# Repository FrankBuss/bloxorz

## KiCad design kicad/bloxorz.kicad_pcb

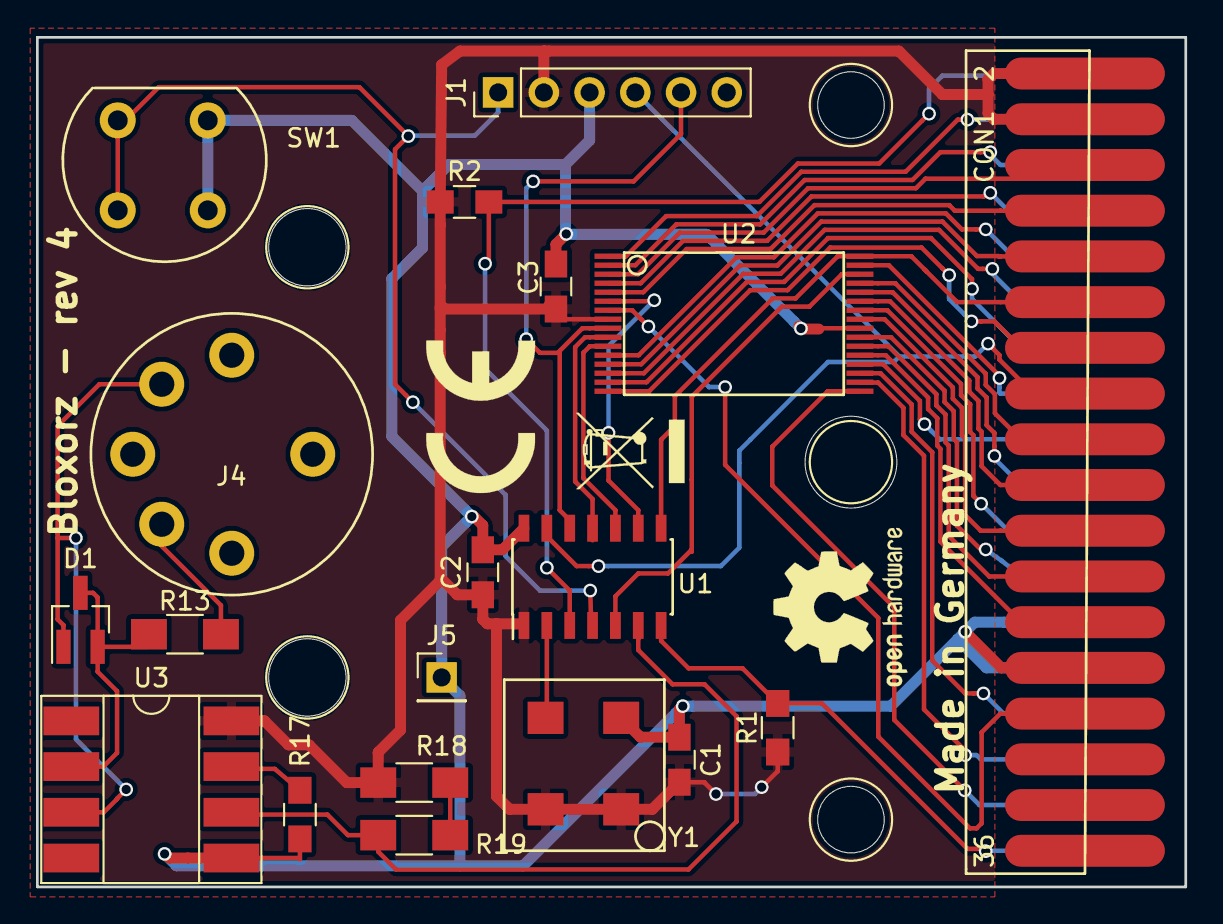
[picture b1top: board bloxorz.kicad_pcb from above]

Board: 2 copper layers, 63.8 x 47.2 mm, 24 parts (0 on the bottom side), 43 nets.

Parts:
C1, C2, C3: 100n; C_0805_HandSoldering
CON1: vectrex-edge-connector; vectrex
D1: BAV99; SOT-23_Handsoldering
J1: PICKIT; Pin_Header_Straight_1x06_Pitch2.54mm
J4: DIN_5; din5
J5: GND; Pin_Header_Straight_1x01_Pitch2.54mm
R1, R2, R17: 10k; R_0805_HandSoldering
R13, R18, R19: 220; R_1206_HandSoldering
SW1: SW_DPST; button
U1: PIC16F18323; SOIC-14_3.9x8.7mm_Pitch1.27mm
U2: SST39SF040-TSOP; TSOP32WH
U3: 6N135; DIP-8_W8.89mm_SMDSocket_LongPads
Y1: 8 MHz oscillator; oscillator
hole1, hole2, hole3, hole4, hole5: 1pin

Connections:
+5V: C1.2, C2.1, C3.2, CON1.2, CON1.4, J1.2, R1.1, R2.1, R18.1, U1.1, U2.8, U3.8, Y1.1, Y1.4
A0: CON1.17, U2.20
A1: CON1.15, U2.31
A2: CON1.13, U2.15
A3: CON1.11, U2.14
A4: CON1.9, U2.12
A5: CON1.7, U2.4
A6: CON1.5, U2.2
A7: CON1.3, U2.1
A8: CON1.6, U2.3
A9: CON1.8, U2.5
A10: CON1.14, U2.16
A11: CON1.10, U2.13
A12: CON1.29, U2.19
A13: CON1.31, U2.18
A14: CON1.33, U2.17
A15: U1.10, U2.11
A16: U1.11, U2.10
A17: U1.9, U2.6
A18: J1.5, U1.12, U2.9
D0: CON1.19, U2.28
D1: CON1.21, U2.26
D2: CON1.23, U2.23
D3: CON1.26, U2.21
D4: CON1.24, U2.22
D5: CON1.22, U2.25
D6: CON1.20, U2.27
D7: CON1.18, U2.29
GND: C1.1, C2.2, C3.1, CON1.25, CON1.27, CON1.28, J1.3, J5.1, R17.2, SW1.2, SW1.4, U1.14, U2.24, U3.5, Y1.2
unnamed: D1.1, J4.5, U3.3
unnamed: D1.2, D1.3, R13.1, U3.2
unnamed: J1.1, SW1.1, SW1.3, U1.4
unnamed: J4.4, R13.2
unnamed: R17.1, U3.7
unnamed: R18.2, R19.1
unnamed: R19.2, U1.6, U3.6
unnamed: U1.2, Y1.3
unnamed: U1.5, U2.30
V-CE: CON1.16, J1.4, U1.13
V-HALT: CON1.1, R2.2, U1.3
V-OE: CON1.12, U1.8, U2.32
V-PB6: CON1.35, R1.2, U1.7
V-RW: CON1.30, U2.7

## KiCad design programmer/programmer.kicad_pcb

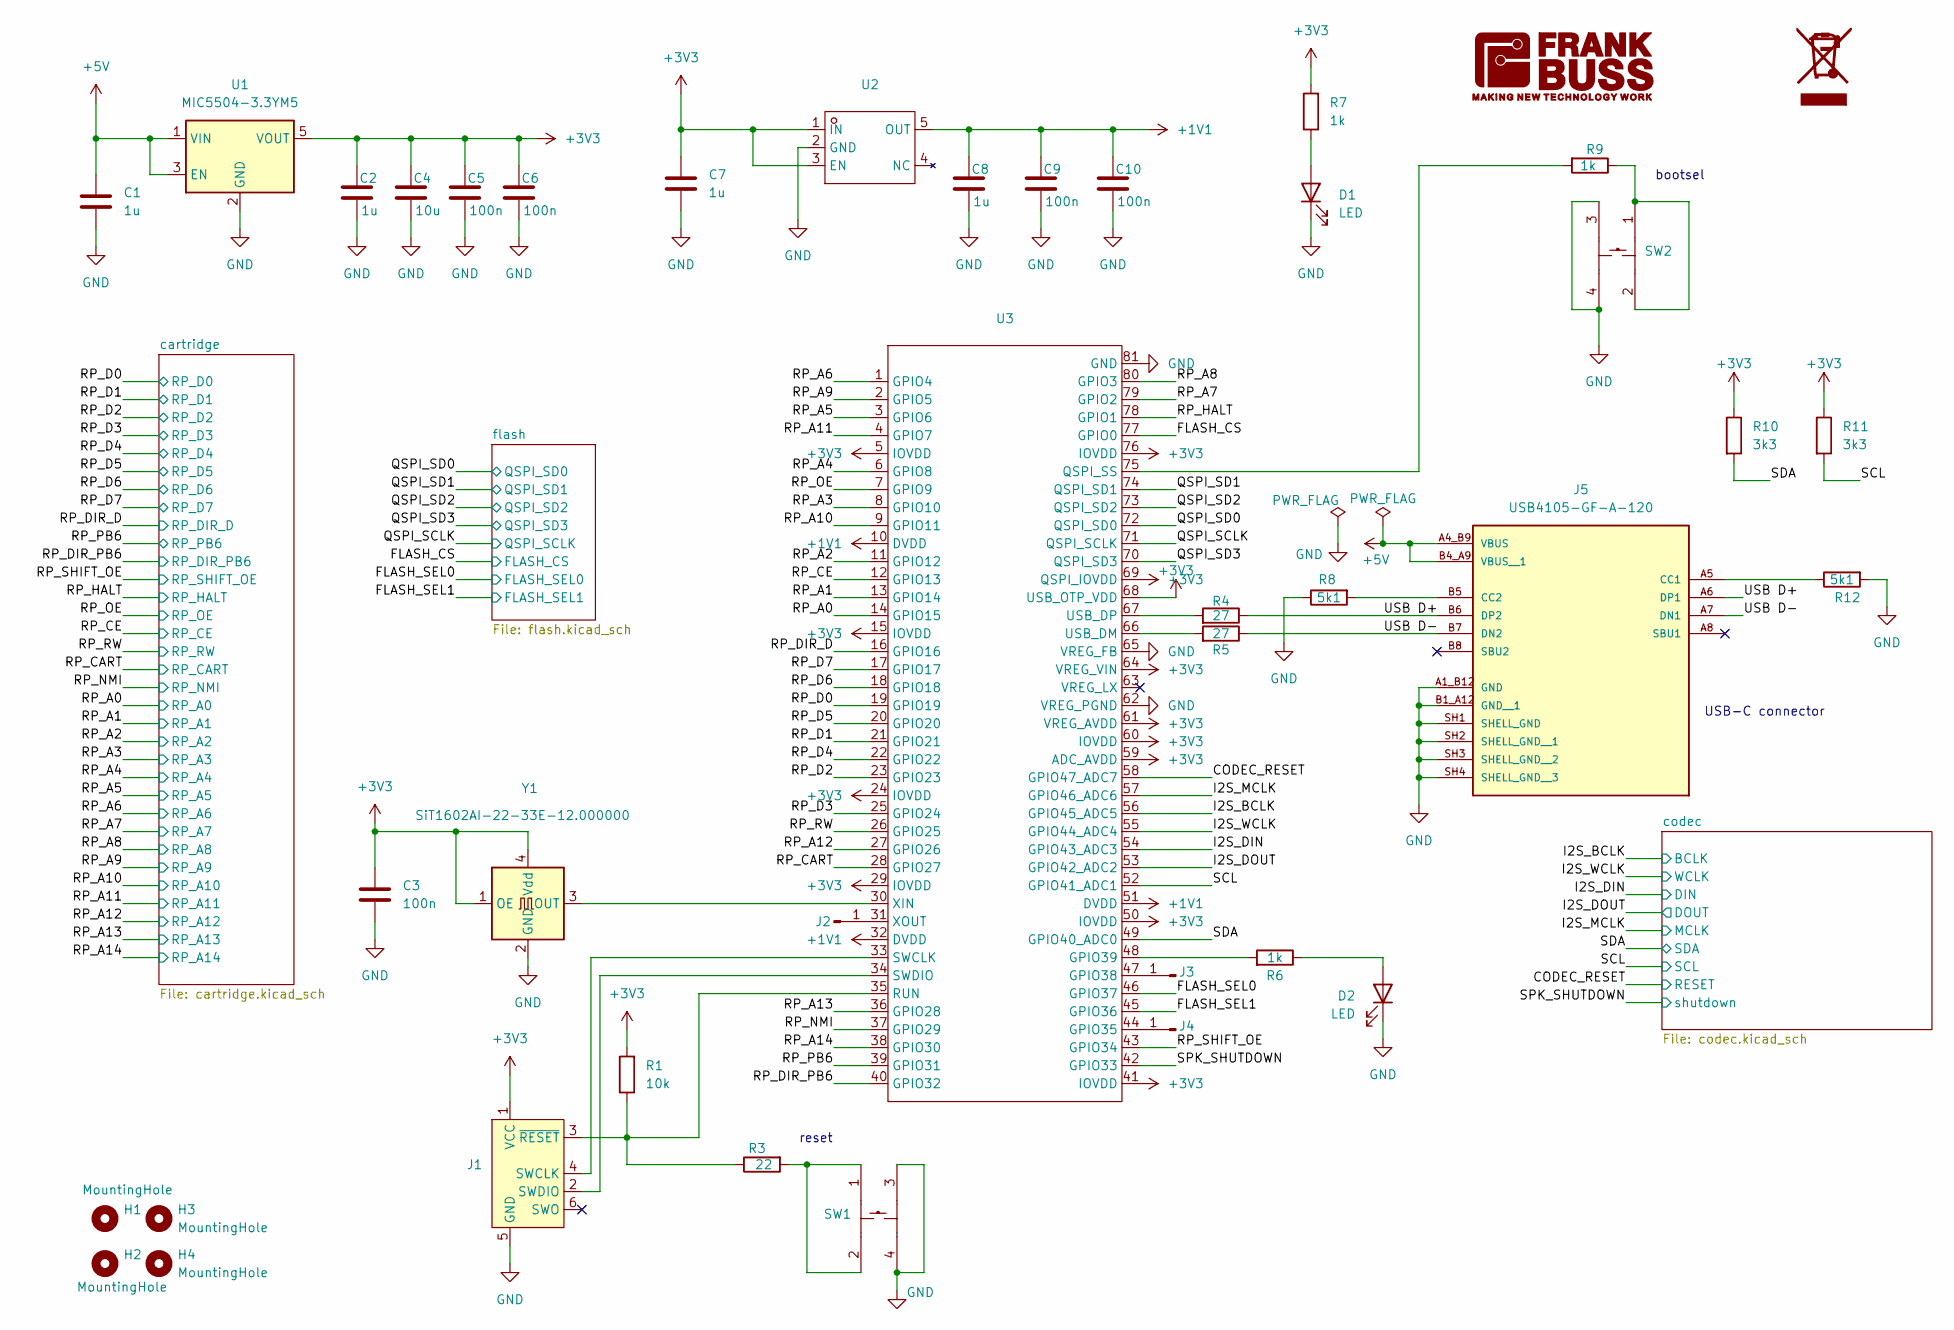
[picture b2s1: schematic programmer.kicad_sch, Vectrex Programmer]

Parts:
C1, C2, C8: 1u; C_0805_2012Metric
C3: 100n; C_0603_1608Metric
C4: 10u; C_0805_2012Metric
C5, C6, C9, C10: 100n; C_0805_2012Metric
C7: 1u; C_0603_1608Metric
D1, D2: LED; LED_0805_2012Metric
G1: Logo_WEEE; WEEE-Logo_8.4x12mm_SilkScreen
G2: Logo_FrankBuss; frank-buss-logo
H1, H2, H3, H4: MountingHole; MountingHole_3.2mm_M3
J1: Conn_ARM_SWD_TagConnect_TC2030-NL; Tag-Connect_TC2030-IDC-NL_2x03_P1.27mm_Vertical
J2, J3, J4: Conn_01x01_Pin; PinHeader_1x01_P2.54mm_Vertical
J5: USB4105-GF-A-120; GCT_USB4105-GF-A-120; PARTREV B3
R1: 10k; R_0603_1608Metric
R3: 22; R_0603_1608Metric
R4, R5: 27; R_0603_1608Metric
R6, R7, R9: 1k; R_0603_1608Metric
R8, R12: 5k1; R_0603_1608Metric
R10, R11: 3k3; R_0603_1608Metric
SW1, SW2: KEY-SMD_4P-L6.0-W6.0-P4.50-LS9.0; Manufacturer Part TS-1002S-07026C; LCSC Part Name 6*6*7mm 立贴 轻触开关
U1: MIC5504-3.3YM5; SOT-23-5
U2: SOT-23-5_L3.0-W1.7-P0.95-LS2.8-BL; Manufacturer Part TLV74311PDBVR; LCSC Part Name 具有使能功能的 300mA、低 IQ、低压降稳压器
U3: QFN-80_L10.0-W10.0-P0.40-TL-EP3.4; Manufacturer Part RP2354B; LCSC Part Name RP2354B
Y1: SiT1602AI-22-33E-12.000000; Oscillator_SMD_SiTime_SiT1602-4Pin_3.2x2.5mm; MPN SiT1602AI-22-33E-12.000000; LCSC C830041

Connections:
+1V1: C8.1, C9.1, C10.1, U2.5 (OUT), U3.10 (DVDD), U3.32 (DVDD), U3.51 (DVDD)
+3V3: C2.1, C3.1, C4.1, C5.1, C6.1, C7.1, J1.1 (VCC), R1.2, R7.2, R10.1, R11.1, U1.5 (VOUT), U2.1 (IN), U2.3 (EN), U3.5 (IOVDD), U3.15 (IOVDD), U3.24 (IOVDD), U3.29 (IOVDD), U3.41 (IOVDD), U3.50 (IOVDD), U3.59 (ADC_AVDD), U3.60 (IOVDD), U3.61 (VREG_AVDD), U3.64 (VREG_VIN), U3.68 (USB_OTP_VDD), U3.69 (QSPI_IOVDD), U3.76 (IOVDD), Y1.1 (OE), Y1.4 (Vdd); also elsewhere on the board
+5V: C1.1, J5.A4_B9 (VBUS), J5.B4_A9 (VBUS__1), U1.1 (VIN), U1.3 (EN); also elsewhere on the board
/CODEC_RESET: U3.58 (GPIO47_ADC7); also elsewhere on the board
/FLASH_CS: U3.77 (GPIO0); also elsewhere on the board
/FLASH_SEL0: U3.46 (GPIO37); also elsewhere on the board
/FLASH_SEL1: U3.45 (GPIO36); also elsewhere on the board
/I2S_BCLK: U3.56 (GPIO45_ADC5); also elsewhere on the board
/I2S_DIN: U3.54 (GPIO43_ADC3); also elsewhere on the board
/I2S_DOUT: U3.53 (GPIO42_ADC2); also elsewhere on the board
/I2S_MCLK: U3.57 (GPIO46_ADC6); also elsewhere on the board
/I2S_WCLK: U3.55 (GPIO44_ADC4); also elsewhere on the board
/QSPI_SCLK: U3.71 (QSPI_SCLK); also elsewhere on the board
/QSPI_SD0: U3.72 (QSPI_SD0); also elsewhere on the board
/QSPI_SD1: U3.74 (QSPI_SD1); also elsewhere on the board
/QSPI_SD2: U3.73 (QSPI_SD2); also elsewhere on the board
/QSPI_SD3: U3.70 (QSPI_SD3); also elsewhere on the board
/RP_A0: U3.14 (GPIO15); also elsewhere on the board
/RP_A1: U3.13 (GPIO14); also elsewhere on the board
/RP_A2: U3.11 (GPIO12); also elsewhere on the board
/RP_A3: U3.8 (GPIO10); also elsewhere on the board
/RP_A4: U3.6 (GPIO8); also elsewhere on the board
/RP_A5: U3.3 (GPIO6); also elsewhere on the board
/RP_A6: U3.1 (GPIO4); also elsewhere on the board
/RP_A7: U3.79 (GPIO2); also elsewhere on the board
/RP_A8: U3.80 (GPIO3); also elsewhere on the board
/RP_A9: U3.2 (GPIO5); also elsewhere on the board
/RP_A10: U3.9 (GPIO11); also elsewhere on the board
/RP_A11: U3.4 (GPIO7); also elsewhere on the board
/RP_A12: U3.27 (GPIO26); also elsewhere on the board
/RP_A13: U3.36 (GPIO28); also elsewhere on the board
/RP_A14: U3.38 (GPIO30); also elsewhere on the board
/RP_CART: U3.28 (GPIO27); also elsewhere on the board
/RP_CE: U3.12 (GPIO13); also elsewhere on the board
/RP_D0: U3.19 (GPIO19); also elsewhere on the board
/RP_D1: U3.21 (GPIO21); also elsewhere on the board
/RP_D2: U3.23 (GPIO23); also elsewhere on the board
/RP_D3: U3.25 (GPIO24); also elsewhere on the board
/RP_D4: U3.22 (GPIO22); also elsewhere on the board
/RP_D5: U3.20 (GPIO20); also elsewhere on the board
/RP_D6: U3.18 (GPIO18); also elsewhere on the board
/RP_D7: U3.17 (GPIO17); also elsewhere on the board
/RP_DIR_D: U3.16 (GPIO16); also elsewhere on the board
/RP_DIR_PB6: U3.40 (GPIO32); also elsewhere on the board
/RP_HALT: U3.78 (GPIO1); also elsewhere on the board
/RP_NMI: U3.37 (GPIO29); also elsewhere on the board
/RP_OE: U3.7 (GPIO9); also elsewhere on the board
/RP_PB6: U3.39 (GPIO31); also elsewhere on the board
/RP_RW: U3.26 (GPIO25); also elsewhere on the board
/RP_SHIFT_OE: U3.43 (GPIO34); also elsewhere on the board
/SCL: R11.2, U3.52 (GPIO41_ADC1); also elsewhere on the board
/SDA: R10.2, U3.49 (GPIO40_ADC0); also elsewhere on the board
/SPK_SHUTDOWN: U3.42 (GPIO33); also elsewhere on the board
/USB D+: J5.A6 (DP1), J5.B6 (DP2), R4.1
/USB D-: J5.A7 (DN1), J5.B7 (DN2), R5.1
GND: C1.2, C2.2, C3.2, C4.2, C5.2, C6.2, C7.2, C8.2, C9.2, C10.2, D1.1 (K), D2.1 (K), J1.5 (GND), J5.A1_B12 (GND), J5.B1_A12 (GND__1), J5.SH1 (SHELL_GND), J5.SH2 (SHELL_GND__1), J5.SH3 (SHELL_GND__2), J5.SH4 (SHELL_GND__3), R8.1, R12.2, SW1.3, SW1.4, SW2.3, SW2.4, U1.2 (GND), U2.2 (GND), U3.62 (VREG_PGND), U3.65 (VREG_FB), U3.81 (GND), Y1.2 (GND); also elsewhere on the board
unnamed: D1.2 (A), R7.1
unnamed: D2.2 (A), R6.1
unnamed: J1.4 (SWCLK), U3.33 (SWCLK)
unnamed: J1.2 (SWDIO), U3.34 (SWDIO)
unnamed: J1.3 (~RESET), R1.1, R3.1, U3.35 (RUN)
unnamed: J2.1, U3.31 (XOUT)
unnamed: J3.1, U3.47 (GPIO38)
unnamed: J4.1, U3.44 (GPIO35)
unnamed: J5.A5 (CC1), R12.1
unnamed: J5.B5 (CC2), R8.2
unnamed: R3.2, SW1.1, SW1.2
unnamed: R9.1, SW2.1, SW2.2
unnamed: R6.2, U3.48 (GPIO39)
unnamed: R9.2, U3.75 (QSPI_SS)
unnamed: R5.2, U3.66 (USB_DM)
unnamed: R4.2, U3.67 (USB_DP)
unnamed: U3.30 (XIN), Y1.3 (OUT)

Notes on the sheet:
bootsel
reset
USB-C connector

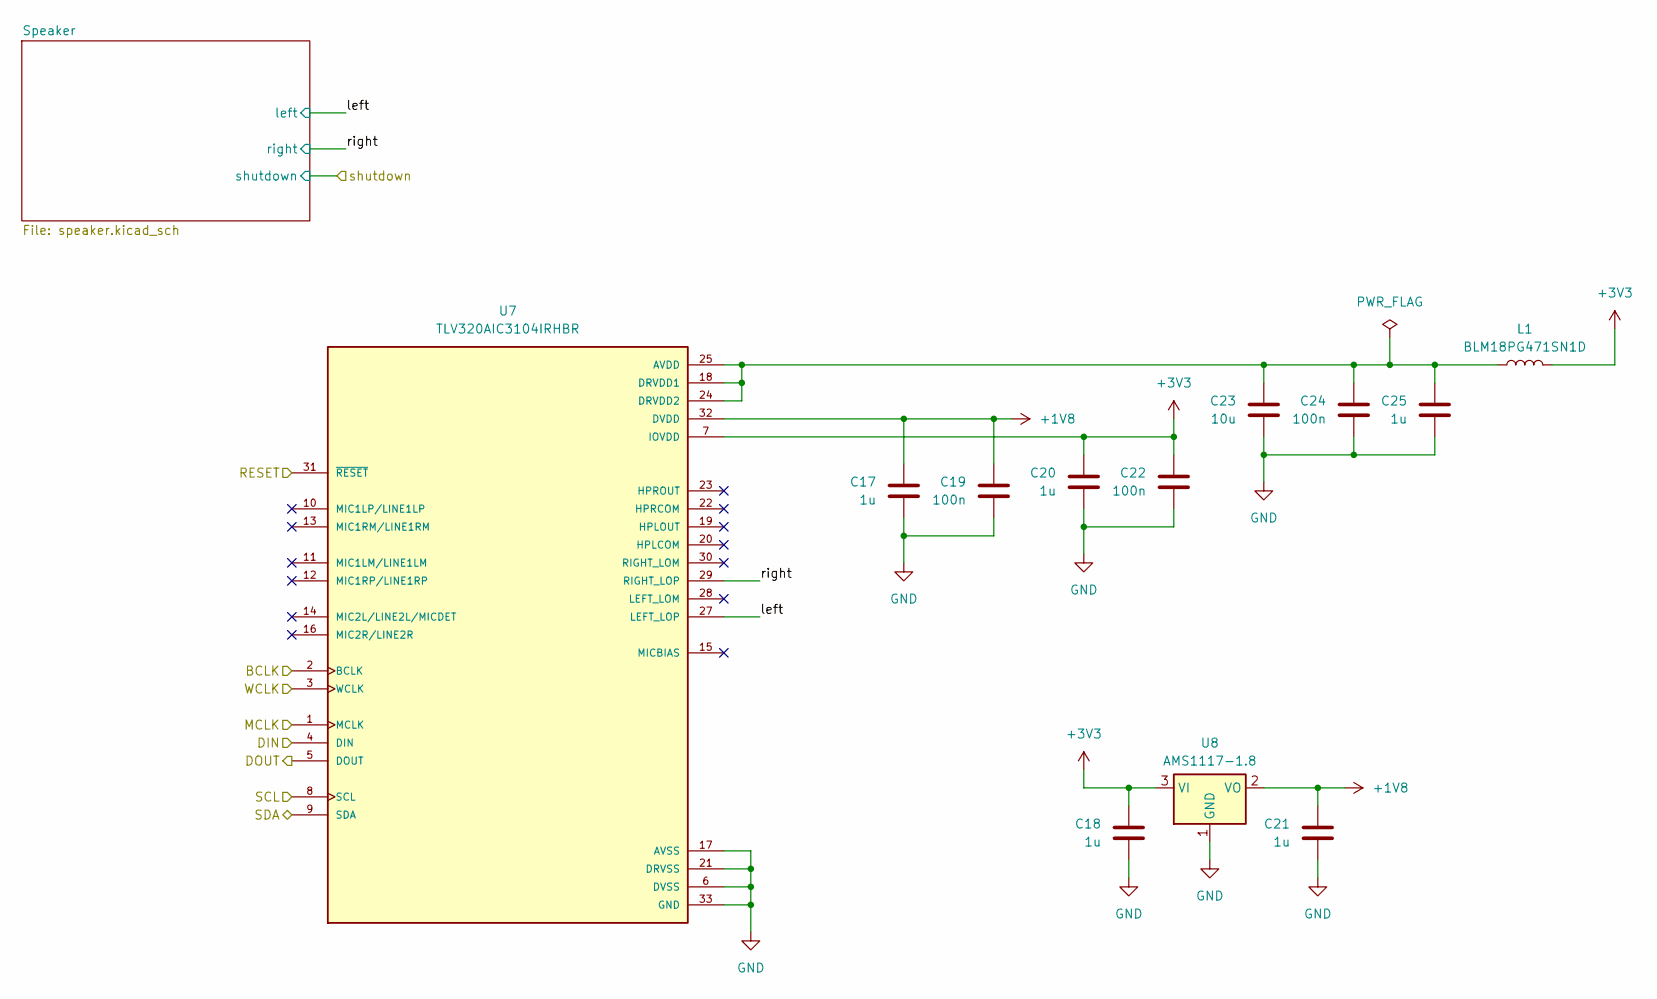
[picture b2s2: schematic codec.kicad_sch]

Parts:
C17, C18, C20, C21, C25: 1u; C_0603_1608Metric
C19, C22, C24: 100n; C_0603_1608Metric
C23: 10u; C_0603_1608Metric
L1: BLM18PG471SN1D; L_0603_1608Metric
U7: TLV320AIC3104IRHBR; QFN50P500X500X100-33N; DigiKey_Part_Number 296-26818-1-ND
U8: AMS1117-1.8; SOT-223-3_TabPin2

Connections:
+1V8: C17.1, C19.1, C21.1, U7.32 (DVDD), U8.2 (VO)
+3V3: C18.1, C20.1, C22.1, L1.1, U7.7 (IOVDD), U8.3 (VI); also elsewhere on the board
/CODEC_RESET: U7.31 (~RESET); also elsewhere on the board
/I2S_BCLK: U7.2 (BCLK); also elsewhere on the board
/I2S_DIN: U7.4 (DIN); also elsewhere on the board
/I2S_DOUT: U7.5 (DOUT); also elsewhere on the board
/I2S_MCLK: U7.1 (MCLK); also elsewhere on the board
/I2S_WCLK: U7.3 (WCLK); also elsewhere on the board
/SCL: U7.8 (SCL); also elsewhere on the board
/SDA: U7.9 (SDA); also elsewhere on the board
/codec/left: U7.27 (LEFT_LOP); also elsewhere on the board
/codec/right: U7.29 (RIGHT_LOP); also elsewhere on the board
GND: C17.2, C18.2, C19.2, C20.2, C21.2, C22.2, C23.2, C24.2, C25.2, U7.6 (DVSS), U7.17 (AVSS), U7.21 (DRVSS), U7.26 (GND), U7.33 (GND), U7.33_1 (GND), U7.33_2 (GND), U7.33_3 (GND), U7.33_4 (GND), U7.33_5 (GND), U7.33_6 (GND), U7.33_7 (GND), U7.33_8 (GND), U7.33_9 (GND), U8.1 (GND); also elsewhere on the board
unnamed: C23.1, C24.1, C25.1, L1.2, U7.18 (DRVDD1), U7.24 (DRVDD2), U7.25 (AVDD)

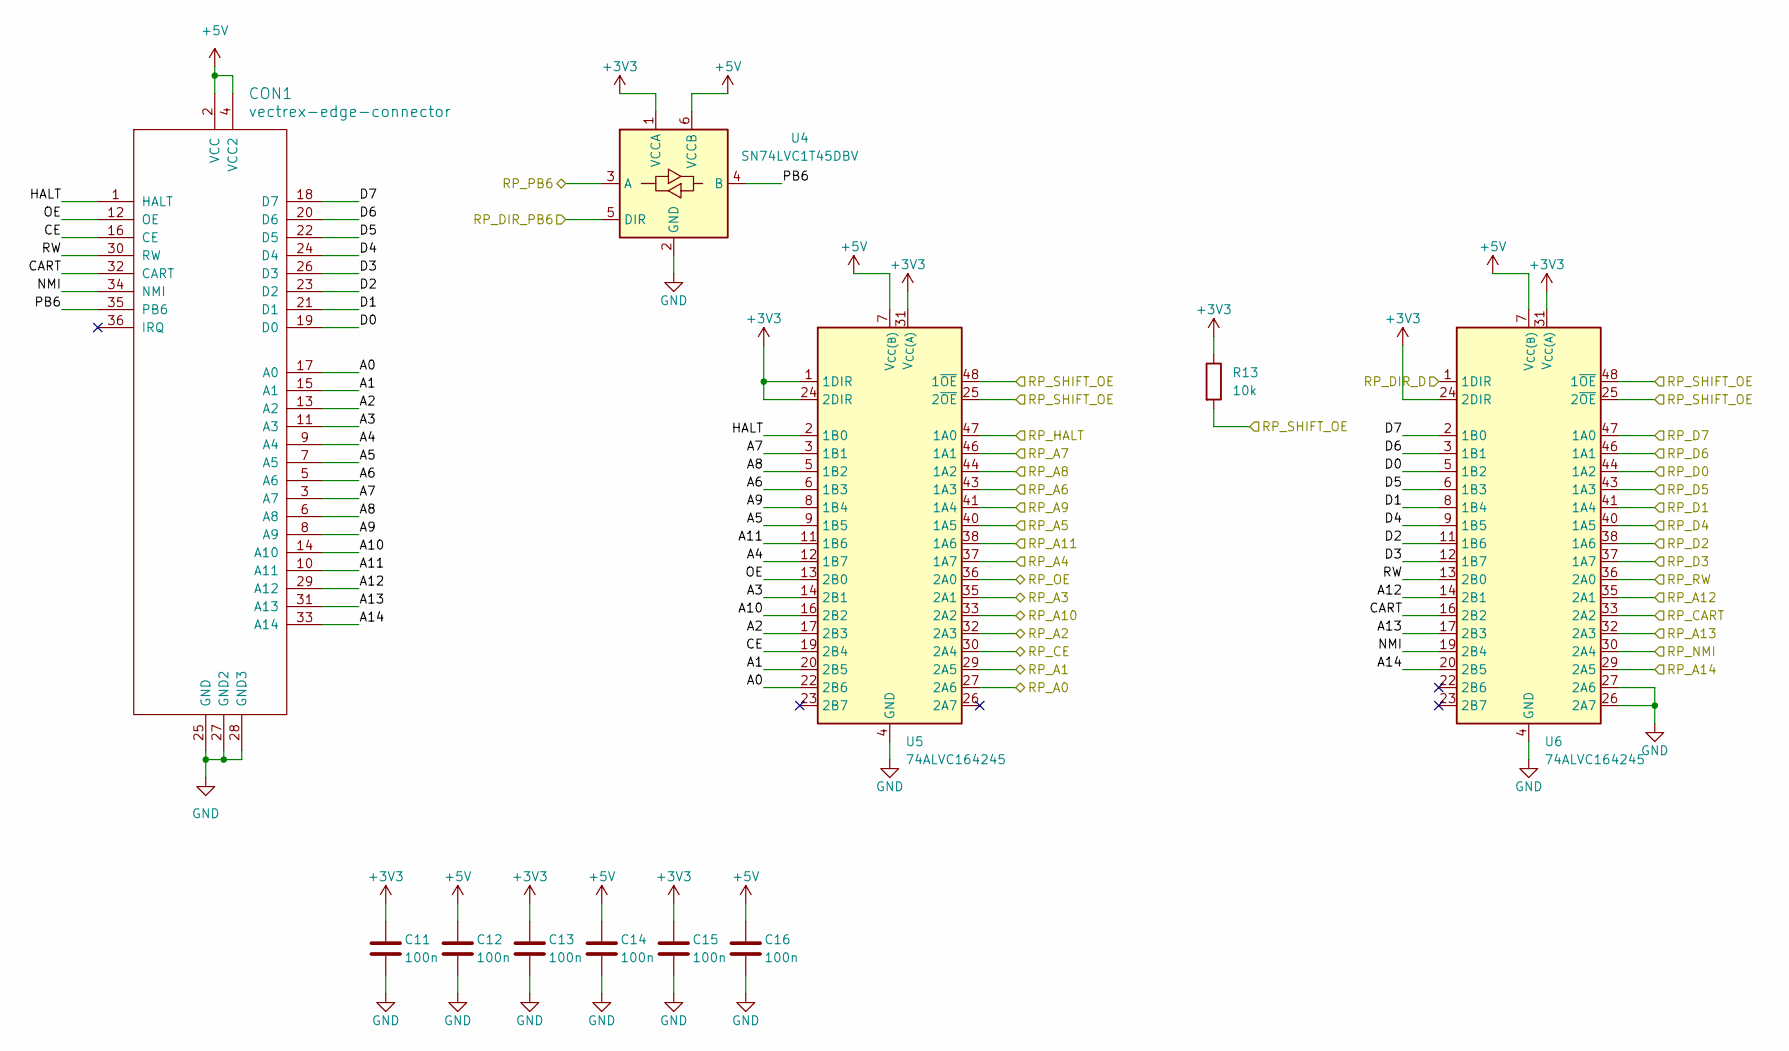
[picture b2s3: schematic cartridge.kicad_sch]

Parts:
C11, C12, C13, C14, C15, C16: 100n; C_0603_1608Metric
CON1: vectrex-edge-connector; vectrex; MPN WingTAT ED36BGFBK; LCSC C5173302
R13: 10k; R_0603_1608Metric
U4: SN74LVC1T45DBV; SOT-23-6
U5, U6: 74ALVC164245; TSSOP-48_6.1x12.5mm_P0.5mm

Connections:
+3V3: C11.1, C13.1, C15.1, R13.1, U4.1 (VCCA), U5.1 (1DIR), U5.24 (2DIR), U5.31 (V_{CC(A)}), U5.42 (V_{CC(A)}), U6.24 (2DIR), U6.31 (V_{CC(A)}), U6.42 (V_{CC(A)}); also elsewhere on the board
+5V: C12.1, C14.1, C16.1, CON1.2 (VCC), CON1.4 (VCC2), U4.6 (VCCB), U5.7 (V_{CC(B)}), U5.18 (V_{CC(B)}), U6.7 (V_{CC(B)}), U6.18 (V_{CC(B)}); also elsewhere on the board
/RP_A0: U5.27 (2A6); also elsewhere on the board
/RP_A1: U5.29 (2A5); also elsewhere on the board
/RP_A2: U5.32 (2A3); also elsewhere on the board
/RP_A3: U5.35 (2A1); also elsewhere on the board
/RP_A4: U5.37 (1A7); also elsewhere on the board
/RP_A5: U5.40 (1A5); also elsewhere on the board
/RP_A6: U5.43 (1A3); also elsewhere on the board
/RP_A7: U5.46 (1A1); also elsewhere on the board
/RP_A8: U5.44 (1A2); also elsewhere on the board
/RP_A9: U5.41 (1A4); also elsewhere on the board
/RP_A10: U5.33 (2A2); also elsewhere on the board
/RP_A11: U5.38 (1A6); also elsewhere on the board
/RP_A12: U6.35 (2A1); also elsewhere on the board
/RP_A13: U6.32 (2A3); also elsewhere on the board
/RP_A14: U6.29 (2A5); also elsewhere on the board
/RP_CART: U6.33 (2A2); also elsewhere on the board
/RP_CE: U5.30 (2A4); also elsewhere on the board
/RP_D0: U6.44 (1A2); also elsewhere on the board
/RP_D1: U6.41 (1A4); also elsewhere on the board
/RP_D2: U6.38 (1A6); also elsewhere on the board
/RP_D3: U6.37 (1A7); also elsewhere on the board
/RP_D4: U6.40 (1A5); also elsewhere on the board
/RP_D5: U6.43 (1A3); also elsewhere on the board
/RP_D6: U6.46 (1A1); also elsewhere on the board
/RP_D7: U6.47 (1A0); also elsewhere on the board
/RP_DIR_D: U6.1 (1DIR); also elsewhere on the board
/RP_DIR_PB6: U4.5 (DIR); also elsewhere on the board
/RP_HALT: U5.47 (1A0); also elsewhere on the board
/RP_NMI: U6.30 (2A4); also elsewhere on the board
/RP_OE: U5.36 (2A0); also elsewhere on the board
/RP_PB6: U4.3 (A); also elsewhere on the board
/RP_RW: U6.36 (2A0); also elsewhere on the board
/RP_SHIFT_OE: R13.2, U5.25 (2~OE), U5.48 (1~OE), U6.25 (2~OE), U6.48 (1~OE); also elsewhere on the board
/cartridge/A0: CON1.17 (A0), U5.22 (2B6)
/cartridge/A1: CON1.15 (A1), U5.20 (2B5)
/cartridge/A2: CON1.13 (A2), U5.17 (2B3)
/cartridge/A3: CON1.11 (A3), U5.14 (2B1)
/cartridge/A4: CON1.9 (A4), U5.12 (1B7)
/cartridge/A5: CON1.7 (A5), U5.9 (1B5)
/cartridge/A6: CON1.5 (A6), U5.6 (1B3)
/cartridge/A7: CON1.3 (A7), U5.3 (1B1)
/cartridge/A8: CON1.6 (A8), U5.5 (1B2)
/cartridge/A9: CON1.8 (A9), U5.8 (1B4)
/cartridge/A10: CON1.14 (A10), U5.16 (2B2)
/cartridge/A11: CON1.10 (A11), U5.11 (1B6)
/cartridge/A12: CON1.29 (A12), U6.14 (2B1)
/cartridge/A13: CON1.31 (A13), U6.17 (2B3)
/cartridge/A14: CON1.33 (A14), U6.20 (2B5)
/cartridge/CART: CON1.32 (CART), U6.16 (2B2)
/cartridge/CE: CON1.16 (CE), U5.19 (2B4)
/cartridge/D0: CON1.19 (D0), U6.5 (1B2)
/cartridge/D1: CON1.21 (D1), U6.8 (1B4)
/cartridge/D2: CON1.23 (D2), U6.11 (1B6)
/cartridge/D3: CON1.26 (D3), U6.12 (1B7)
/cartridge/D4: CON1.24 (D4), U6.9 (1B5)
/cartridge/D5: CON1.22 (D5), U6.6 (1B3)
/cartridge/D6: CON1.20 (D6), U6.3 (1B1)
/cartridge/D7: CON1.18 (D7), U6.2 (1B0)
/cartridge/HALT: CON1.1 (HALT), U5.2 (1B0)
/cartridge/NMI: CON1.34 (NMI), U6.19 (2B4)
/cartridge/OE: CON1.12 (OE), U5.13 (2B0)
/cartridge/PB6: CON1.35 (PB6), U4.4 (B)
/cartridge/RW: CON1.30 (RW), U6.13 (2B0)
GND: C11.2, C12.2, C13.2, C14.2, C15.2, C16.2, CON1.25 (GND), CON1.27 (GND2), CON1.28 (GND3), U4.2 (GND), U5.4 (GND), U5.10 (GND), U5.15 (GND), U5.21 (GND), U5.28 (GND), U5.34 (GND), U5.39 (GND), U5.45 (GND), U6.4 (GND), U6.10 (GND), U6.15 (GND), U6.21 (GND), U6.26 (2A7), U6.27 (2A6), U6.28 (GND), U6.34 (GND), U6.39 (GND), U6.45 (GND); also elsewhere on the board

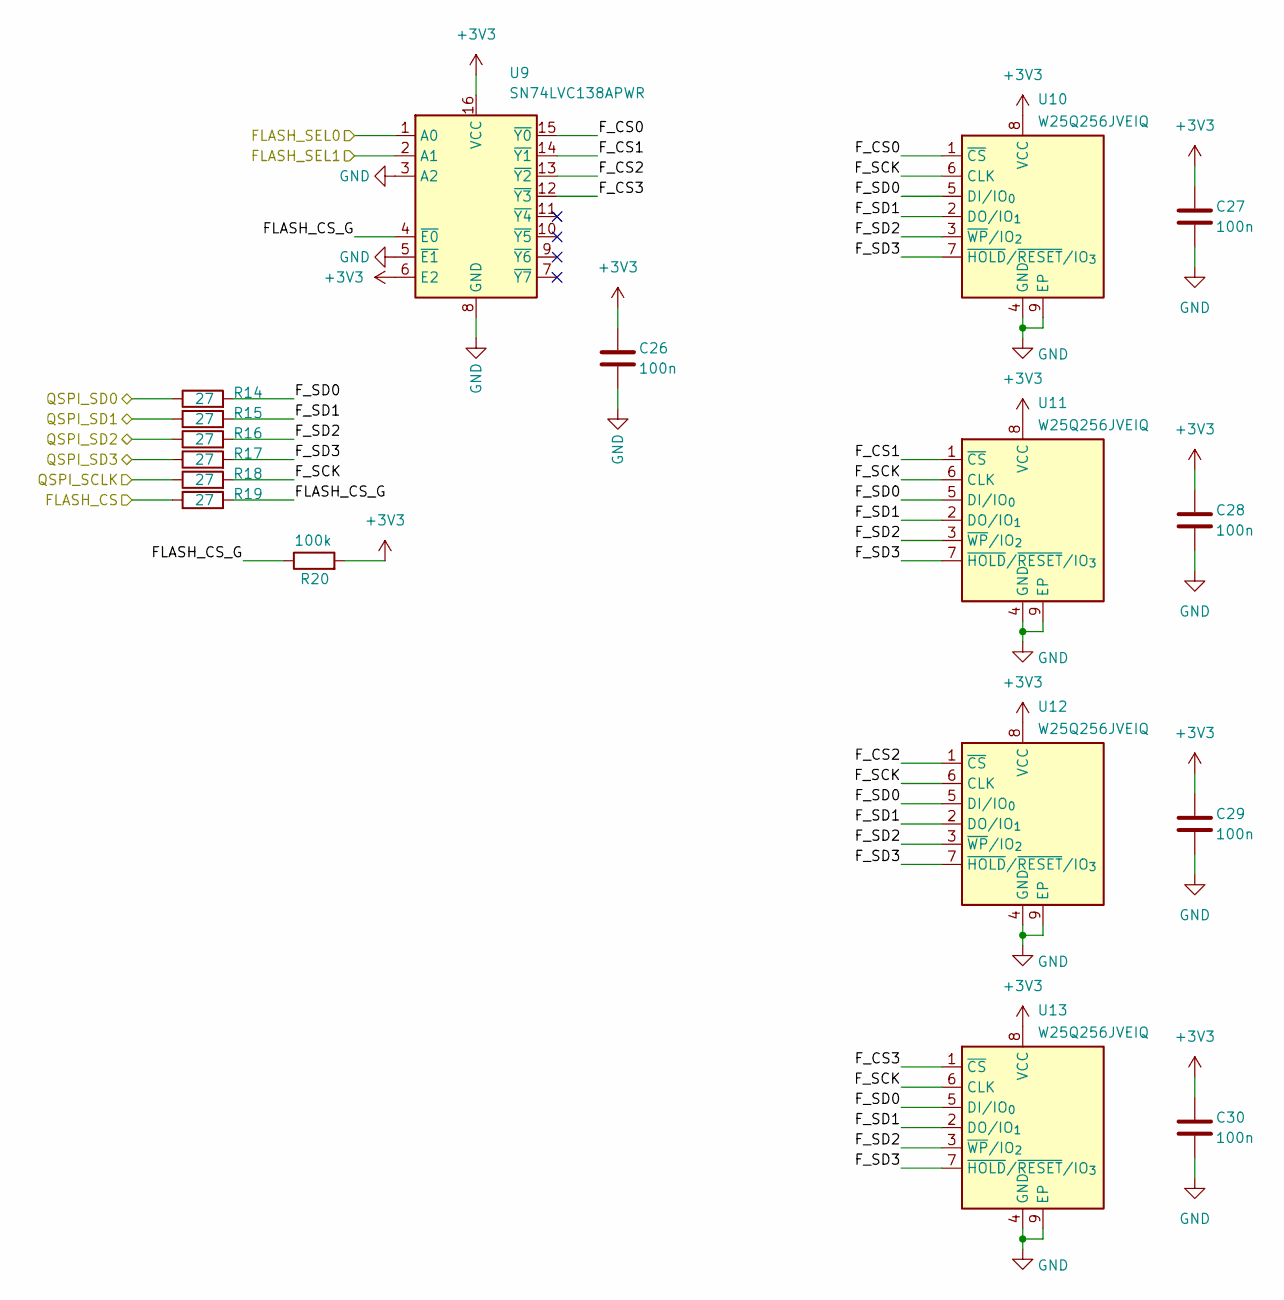
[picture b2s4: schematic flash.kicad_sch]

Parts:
C26, C27, C28, C29, C30: 100n; C_0603_1608Metric
R14, R15, R16, R17, R18, R19: 27; R_0603_1608Metric
R20: 100k; R_0603_1608Metric
U9: SN74LVC138APWR; TSSOP-16_4.4x5mm_P0.65mm
U10, U11, U12, U13: W25Q256JVEIQ; WSON-8-1EP_8x6mm_P1.27mm_EP3.4x4.3mm

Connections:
+3V3: C26.1, C27.1, C28.1, C29.1, C30.1, R20.2, U9.6 (E2), U9.16 (VCC), U10.8 (VCC), U11.8 (VCC), U12.8 (VCC), U13.8 (VCC); also elsewhere on the board
/FLASH_CS: R19.1; also elsewhere on the board
/FLASH_SEL0: U9.1 (A0); also elsewhere on the board
/FLASH_SEL1: U9.2 (A1); also elsewhere on the board
/QSPI_SCLK: R18.1; also elsewhere on the board
/QSPI_SD0: R14.1; also elsewhere on the board
/QSPI_SD1: R15.1; also elsewhere on the board
/QSPI_SD2: R16.1; also elsewhere on the board
/QSPI_SD3: R17.1; also elsewhere on the board
/flash/FLASH_CS_G: R19.2, R20.1, U9.4 (~E0)
/flash/F_CS0: U9.15 (~Y0), U10.1 (~CS)
/flash/F_CS1: U9.14 (~Y1), U11.1 (~CS)
/flash/F_CS2: U9.13 (~Y2), U12.1 (~CS)
/flash/F_CS3: U9.12 (~Y3), U13.1 (~CS)
/flash/F_SCK: R18.2, U10.6 (CLK), U11.6 (CLK), U12.6 (CLK), U13.6 (CLK)
/flash/F_SD0: R14.2, U10.5 (DI/IO_{0}), U11.5 (DI/IO_{0}), U12.5 (DI/IO_{0}), U13.5 (DI/IO_{0})
/flash/F_SD1: R15.2, U10.2 (DO/IO_{1}), U11.2 (DO/IO_{1}), U12.2 (DO/IO_{1}), U13.2 (DO/IO_{1})
/flash/F_SD2: R16.2, U10.3 (~WP/IO_{2}), U11.3 (~WP/IO_{2}), U12.3 (~WP/IO_{2}), U13.3 (~WP/IO_{2})
/flash/F_SD3: R17.2, U10.7 (~HOLD/~RESET/IO_{3}), U11.7 (~HOLD/~RESET/IO_{3}), U12.7 (~HOLD/~RESET/IO_{3}), U13.7 (~HOLD/~RESET/IO_{3})
GND: C26.2, C27.2, C28.2, C29.2, C30.2, U9.3 (A2), U9.5 (~E1), U9.8 (GND), U10.4 (GND), U10.9 (EP), U11.4 (GND), U11.9 (EP), U12.4 (GND), U12.9 (EP), U13.4 (GND), U13.9 (EP); also elsewhere on the board

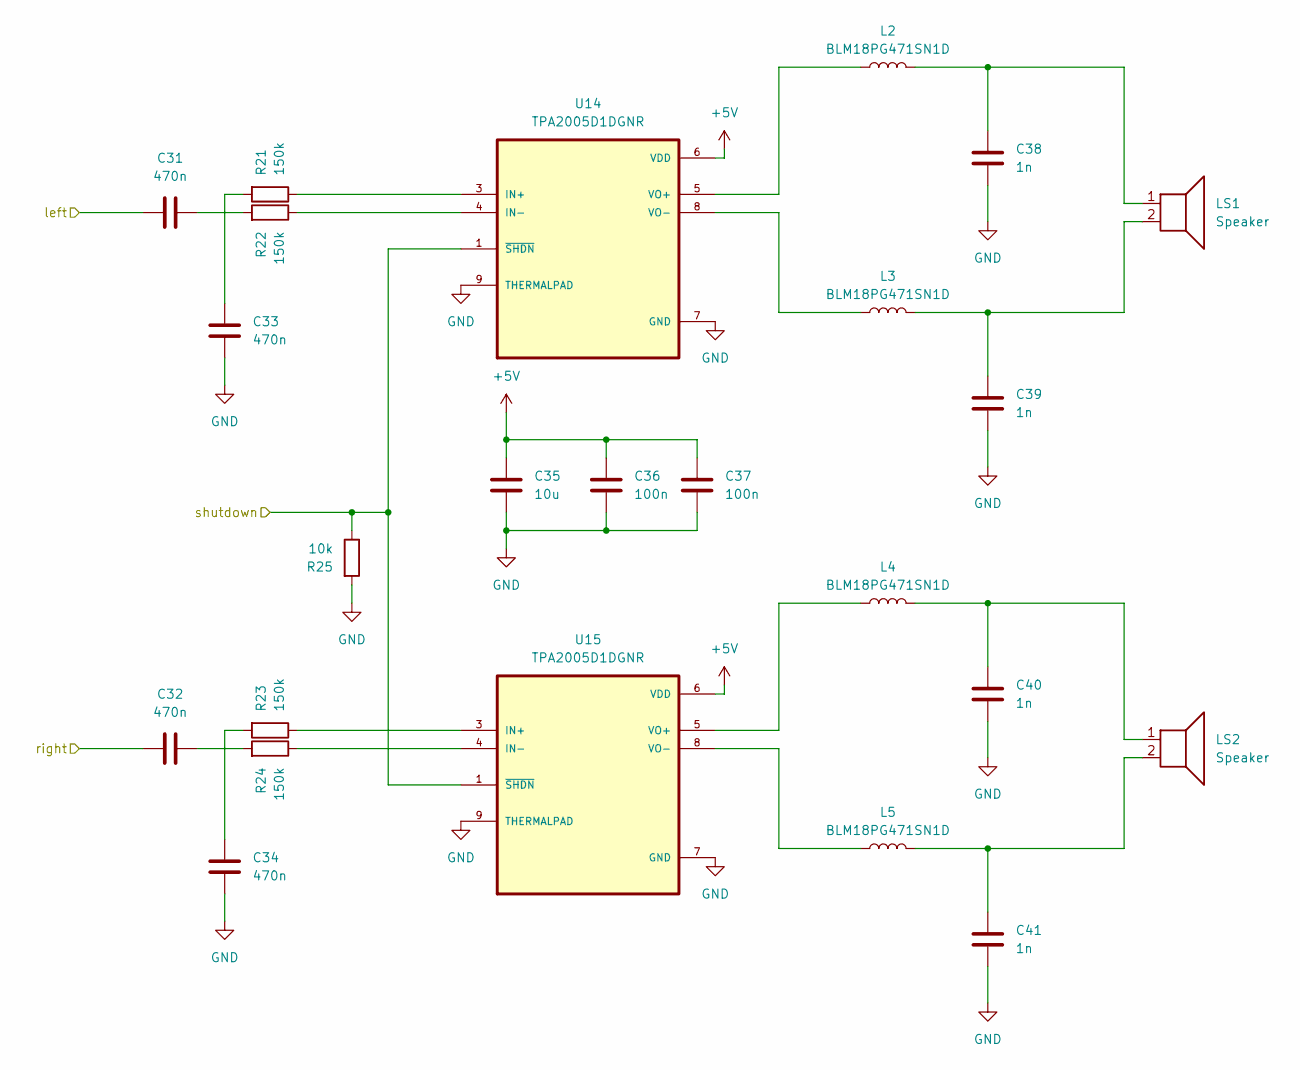
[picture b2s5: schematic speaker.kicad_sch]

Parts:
C31, C32, C33, C34: 470n; C_0603_1608Metric
C35: 10u; C_0603_1608Metric
C36, C37: 100n; C_0603_1608Metric
C38, C39, C40, C41: 1n; C_0603_1608Metric
L2, L3, L4, L5: BLM18PG471SN1D; L_0603_1608Metric
LS1, LS2: Speaker; PinHeader_1x02_P2.54mm_Vertical
R21, R22, R23, R24: 150k; R_0603_1608Metric
R25: 10k; R_0603_1608Metric
U14, U15: TPA2005D1DGNR; SOP65P490X110-9N; DigiKey_Part_Number 296-26876-1-ND

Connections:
+5V: C35.2, C36.2, C37.2, U14.6 (VDD), U15.6 (VDD); also elsewhere on the board
/SPK_SHUTDOWN: R25.1, U14.1 (~SHDN), U15.1 (~SHDN); also elsewhere on the board
/codec/left: C31.1; also elsewhere on the board
/codec/right: C32.1; also elsewhere on the board
GND: C33.2, C34.2, C35.1, C36.1, C37.1, C38.1, C39.1, C40.1, C41.1, R25.2, U14.7 (GND), U14.9 (THERMALPAD), U15.7 (GND), U15.9 (THERMALPAD); also elsewhere on the board
unnamed: C31.2, R22.2
unnamed: C32.2, R24.2
unnamed: C33.1, R21.2
unnamed: C34.1, R23.2
unnamed: C38.2, L2.2, LS1.1
unnamed: C39.2, L3.2, LS1.2
unnamed: C40.2, L4.2, LS2.1
unnamed: C41.2, L5.2, LS2.2
unnamed: R21.1, U14.3 (IN+)
unnamed: R22.1, U14.4 (IN-)
unnamed: L2.1, U14.5 (VO+)
unnamed: L3.1, U14.8 (VO-)
unnamed: R23.1, U15.3 (IN+)
unnamed: R24.1, U15.4 (IN-)
unnamed: L4.1, U15.5 (VO+)
unnamed: L5.1, U15.8 (VO-)

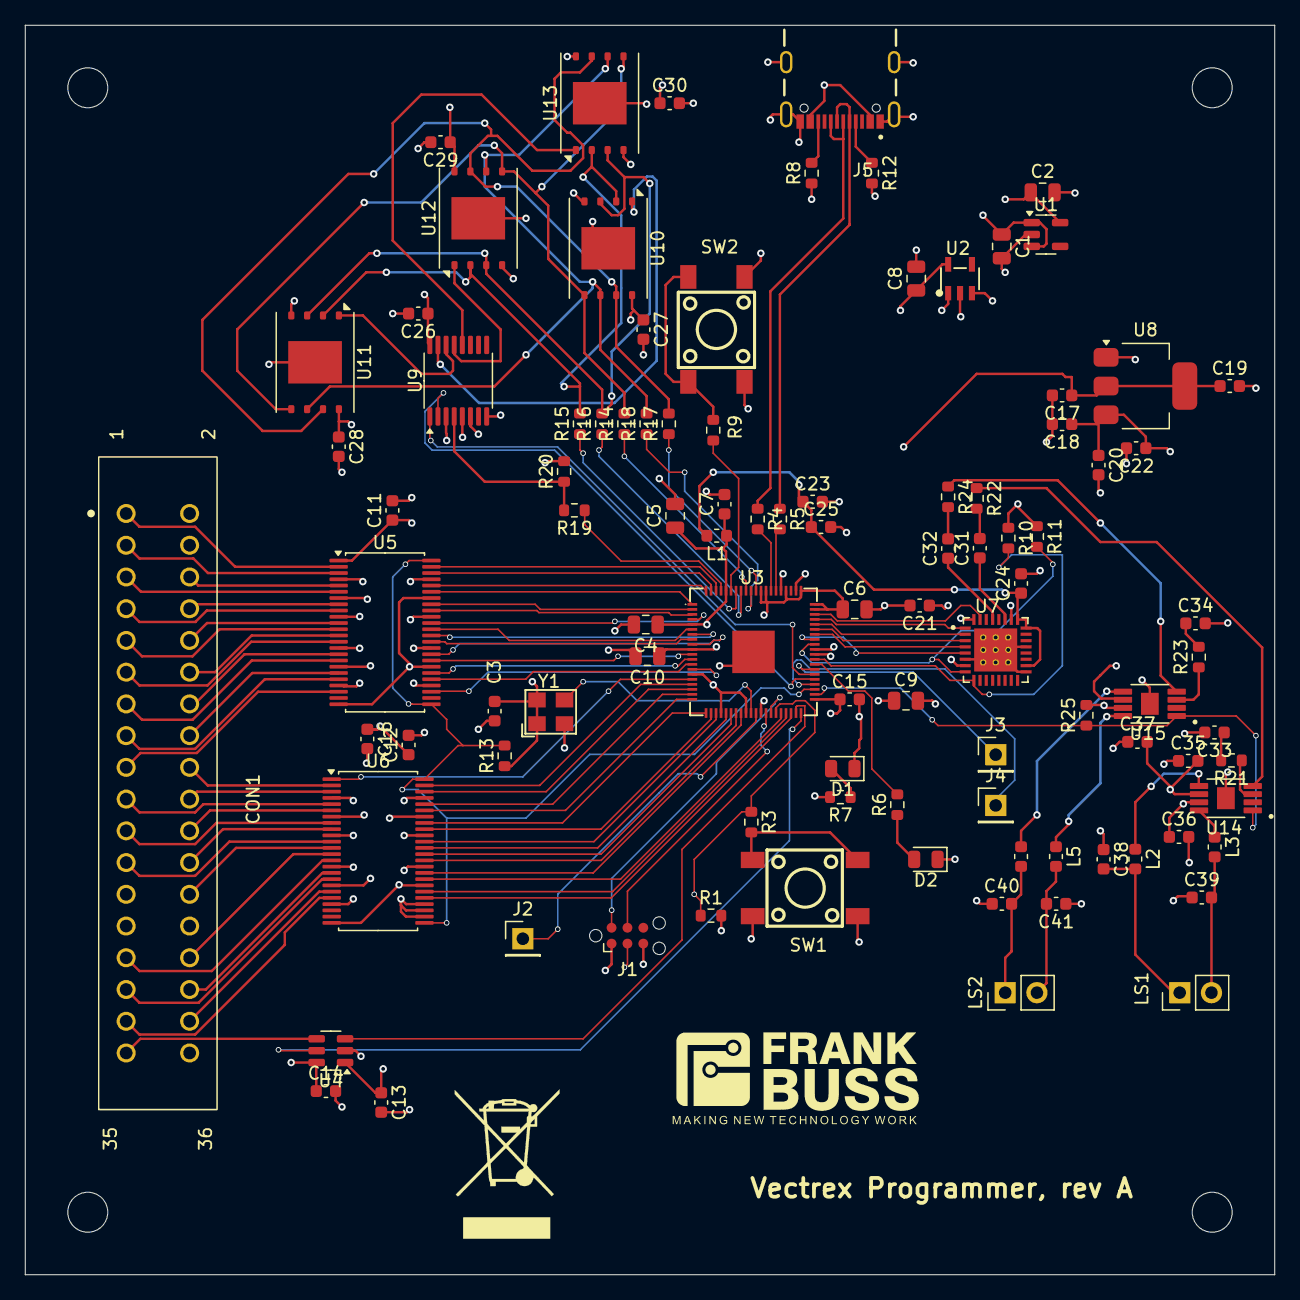
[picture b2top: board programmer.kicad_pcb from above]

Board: 4 copper layers, 100.0 x 100.0 mm, 104 parts (0 on the bottom side), 133 nets.

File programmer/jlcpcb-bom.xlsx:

Comment | Designator | Footprint | JLCPCB Part #
1u | C1,C2,C8 | C_0805_2012Metric | C28323
vectrex-edge-connector | CON1 | vectrex | C5173302
100n | C3,C11,C12,C13,C14,C15,C16,C19,C22,C24,C26,C27,C28,C29,C30,C36,C37 | C_0603_1608Metric | C14663
10u | C4 | C_0805_2012Metric | C15850
100n | C5,C6,C9,C10 | C_0805_2012Metric | C49678
1u | C7,C17,C18,C20,C21,C25 | C_0603_1608Metric | C15849
10u | C23,C35 | C_0603_1608Metric | C380317
470n | C31,C32,C33,C34 | C_0603_1608Metric | C513577
1n | C38,C39,C40,C41 | C_0603_1608Metric | C1588
LED | D1,D2 | LED_0805_2012Metric | C84256
Conn_01x01_Pin | J2,J3,J4 | PinHeader_1x01_P2.54mm_Vertical
USB4105-GF-A-120 | J5 | GCT_USB4105-GF-A-120 | C5184243
BLM18PG471SN1D | L1,L2,L3,L4,L5 | L_0603_1608Metric | C97853
Speaker | LS1,LS2 | PinHeader_1x02_P2.54mm_Vertical
10k | R1,R13,R25 | R_0603_1608Metric | C25804
22 | R3 | R_0603_1608Metric | C23345
27 | R4,R5,R14,R15,R16,R17,R18,R19 | R_0603_1608Metric | C25190
1k | R6,R7,R9 | R_0603_1608Metric | C21190
5k1 | R8,R12 | R_0603_1608Metric | C23186
3k3 | R10,R11 | R_0603_1608Metric | C22978
100k | R20 | R_0603_1608Metric | C25803
150k | R21,R22,R23,R24 | R_0603_1608Metric | C22807
TS-1002S-07026C | SW1,SW2 | KEY-SMD_4P-L6.0-W6.0-P4.50-LS9.0 | C455114
MIC5504-3.3YM5 | U1 | SOT-23-5 | C88419
TLV74311PDBVR | U2 | SOT-23-5_L3.0-W1.7-P0.95-LS2.8-BL | C485147
RP2354B | U3 | QFN-80_L10.0-W10.0-P0.40-TL-EP3.4 | C39843328
SN74LVC1T45DBV | U4 | SOT-23-6 | C7843
74ALVC164245 | U5,U6 | TSSOP-48_6.1x12.5mm_P0.5mm | C7128
TLV320AIC3104IRHBR | U7 | QFN50P500X500X100-33N | C181753
AMS1117-1.8 | U8 | SOT-223-3_TabPin2 | C6185
SN74LVC138APWR | U9 | TSSOP-16_4.4x5mm_P0.65mm | C485077
W25Q256JVEIQ | U10,U11,U12,U13 | WSON-8-1EP_8x6mm_P1.27mm_EP3.4x4.3mm | C97522
TPA2005D1DGNR | U14,U15 | SOP65P490X110-9N | C27396
SiT1602AI-22-33E-12.000000 | Y1 | Oscillator_SMD_SiTime_SiT1602-4Pin_3.2x2.5mm | C830041
